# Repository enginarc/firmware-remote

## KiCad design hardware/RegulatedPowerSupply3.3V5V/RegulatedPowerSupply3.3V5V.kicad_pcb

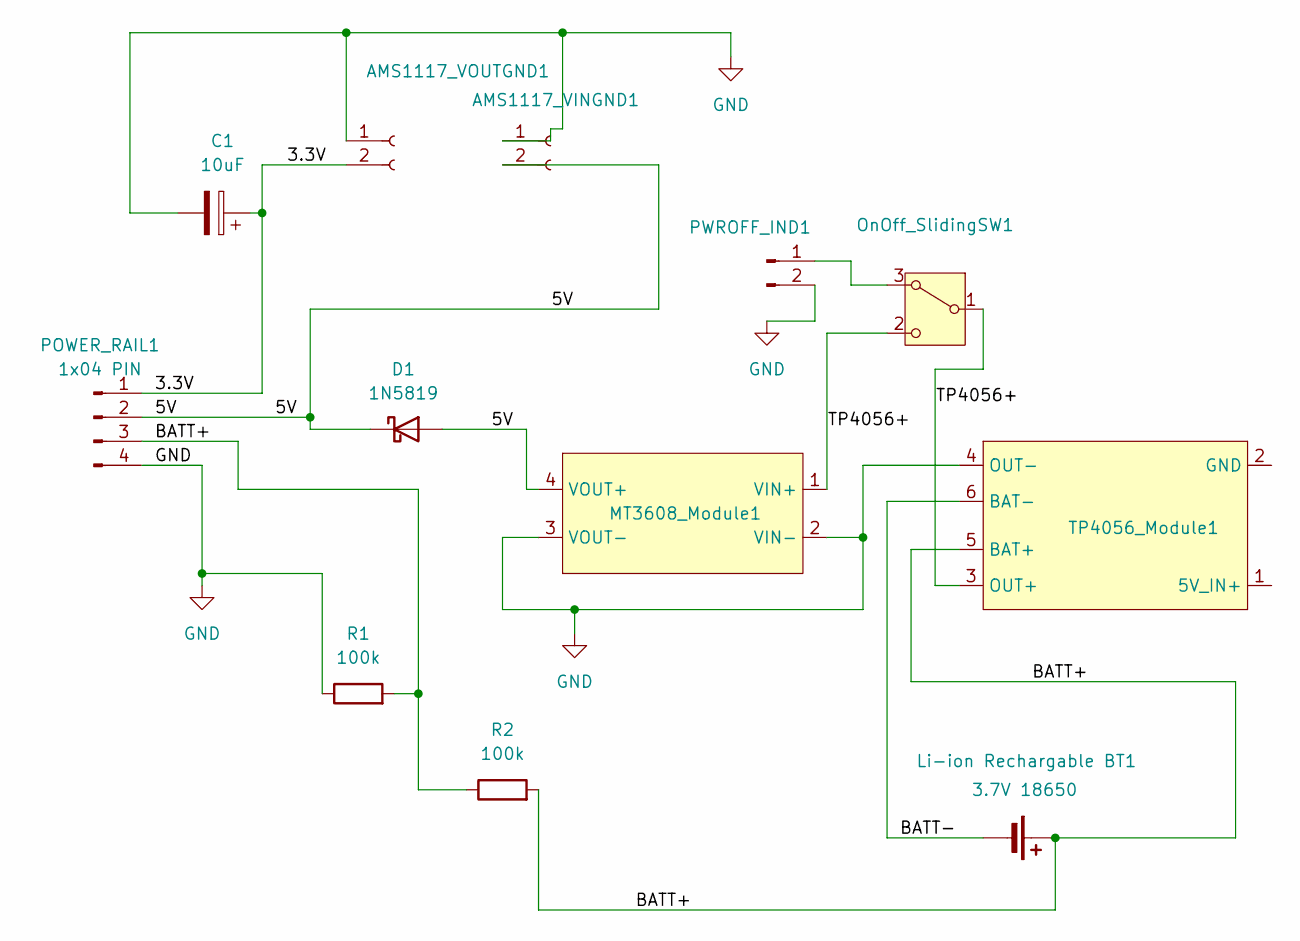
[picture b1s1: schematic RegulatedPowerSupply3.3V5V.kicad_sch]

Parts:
AMS1117_VINGND1, AMS1117_VOUTGND1: 1x02 Pin; PinSocket_1x02_P2.54mm_Vertical
C1: 10uF; CP_Radial_D4.0mm_P2.00mm
D1: 1N5819; D_DO-41_SOD81_P10.16mm_Horizontal
Li-ion Rechargable BT1: 3.7V 18650; BatteryHolder_MPD_BK-18650-PC2
MT3608_Module1: MT3608-hw-045
OnOff_SlidingSW1: SW_Wuerth_450301014042; SW_Slide-03_Wuerth-WS-SLTV_10x2.5x6.4_P2.54mm
POWER_RAIL1: 1x04 PIN; PinHeader_1x04_P2.54mm_Vertical
PWROFF_IND1: Conn_01x02_Pin; PinHeader_1x02_P2.54mm_Vertical
R1, R2: 100k; R_Axial_DIN0207_L6.3mm_D2.5mm_P7.62mm_Horizontal
TP4056_Module1: TP4056-18650

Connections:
/3.3V: AMS1117_VOUTGND1.2, C1.1, POWER_RAIL1.1
/5V: AMS1117_VINGND1.2, D1.1 (K), D1.2 (A), MT3608_Module1.4 (VOUT+), POWER_RAIL1.2
/BATT+: Li-ion Rechargable BT1.1 (+), POWER_RAIL1.3, R1.2, R2.1, R2.2, TP4056_Module1.5 (BAT+)
/BATT-: Li-ion Rechargable BT1.2 (-), TP4056_Module1.6 (BAT-)
/TP4056+: MT3608_Module1.1 (VIN+), OnOff_SlidingSW1.1 (B), OnOff_SlidingSW1.2 (C), TP4056_Module1.3 (OUT+)
GND: AMS1117_VINGND1.1, AMS1117_VOUTGND1.1, C1.2, MT3608_Module1.2 (VIN-), MT3608_Module1.3 (VOUT-), POWER_RAIL1.4, PWROFF_IND1.2, R1.1, TP4056_Module1.4 (OUT-)
unnamed: OnOff_SlidingSW1.3 (A), PWROFF_IND1.1

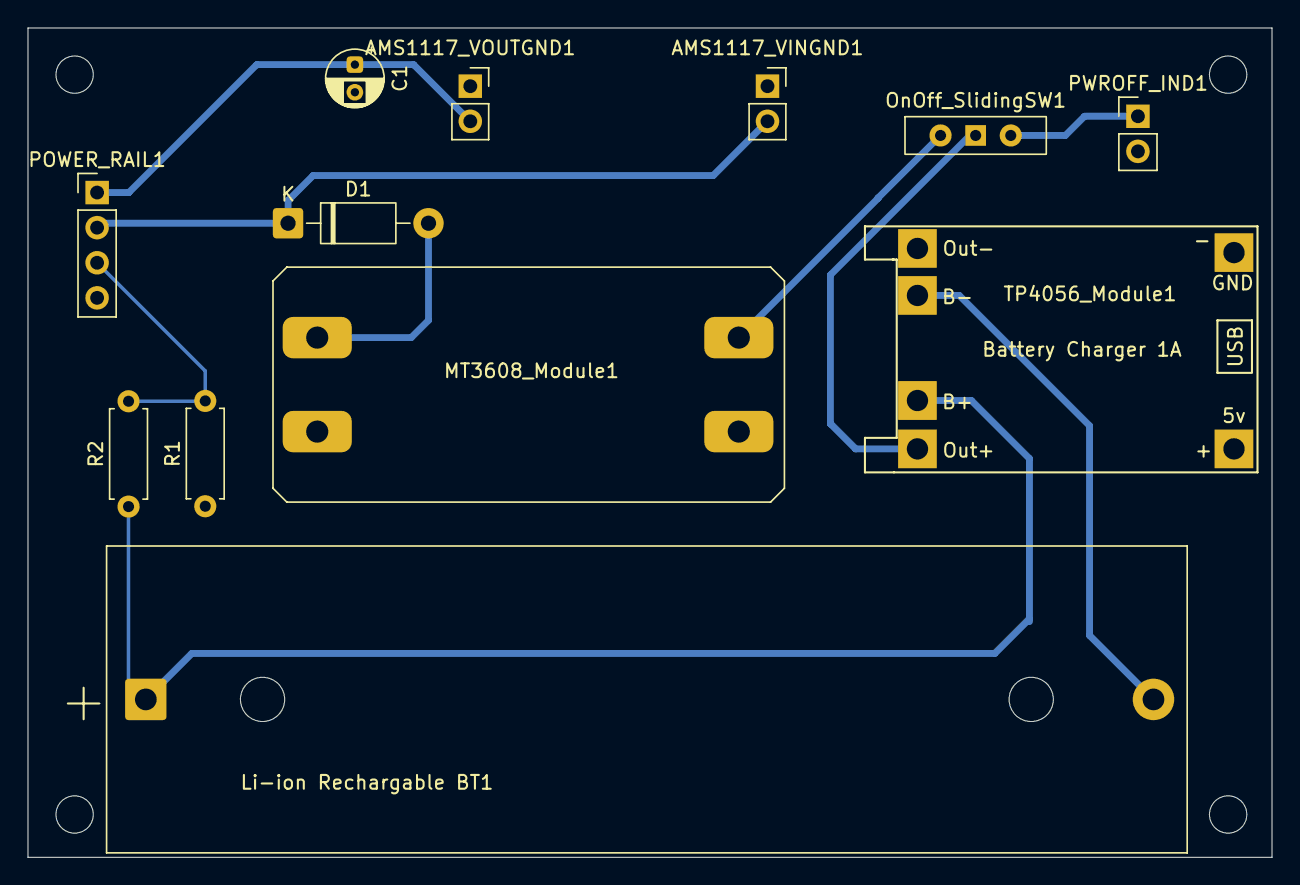
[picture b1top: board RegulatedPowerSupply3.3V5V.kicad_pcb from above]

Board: 2 copper layers, 90.0 x 60.0 mm, 12 parts (0 on the bottom side), 7 nets.

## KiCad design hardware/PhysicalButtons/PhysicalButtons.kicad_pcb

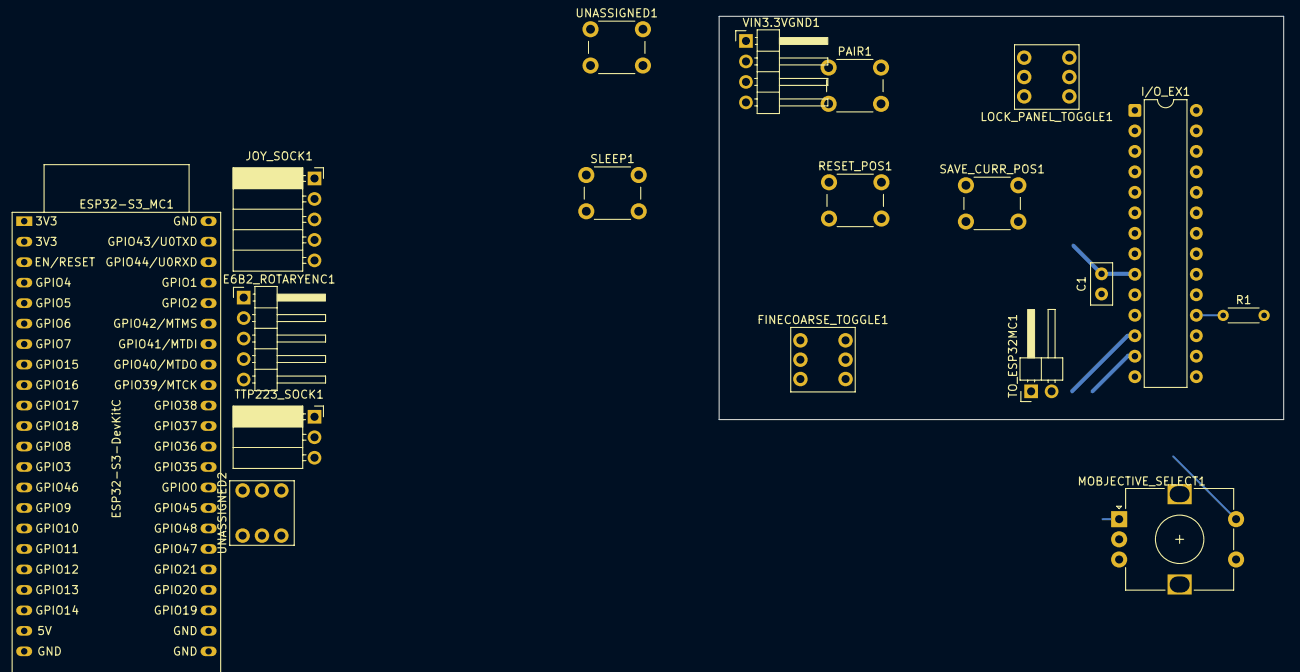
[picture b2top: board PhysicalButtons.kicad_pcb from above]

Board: 2 copper layers, 70.0 x 50.0 mm, 18 parts (0 on the bottom side), 15 nets.

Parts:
C1: 0.1uF; C_Disc_D5.0mm_W2.5mm_P2.50mm
E6B2_ROTARYENC1: Conn_01x05_Pin; PinHeader_1x05_P2.54mm_Horizontal
ESP32-S3_MC1: ESP32-S3-DevKitC
FINECOARSE_TOGGLE1: SW_Push_DPDT; SW_Push_DPDT_8x8mm
I/O_EX1: MCP23017_SP; DIP-28_W7.62mm
JOY_SOCK1: Conn_01x05_Socket; PinSocket_1x05_P2.54mm_Horizontal
LOCK_PANEL_TOGGLE1: SW_Push_DPDT; SW_Push_DPDT_8x8mm
MOBJECTIVE_SELECT1: RotaryEncoder_Switch; RotaryEncoder_Alps_EC12E-Switch_Vertical_H20mm
PAIR1: SW_Push; SW_PUSH_6mm_H8.5mm
R1: 10R; R_Axial_DIN0204_L3.6mm_D1.6mm_P5.08mm_Horizontal
RESET_POS1: SW_Push; SW_PUSH_6mm_H8.5mm
SAVE_CURR_POS1: SW_Push; SW_PUSH_6mm_H8.5mm
SLEEP1: SW_Push; SW_PUSH_6mm_H8.5mm
TO_ESP32MC1: Conn_01x02_Pin; PinHeader_1x02_P2.54mm_Horizontal
TTP223_SOCK1: Conn_01x03_Socket; PinSocket_1x03_P2.54mm_Horizontal
UNASSIGNED1: SW_Push; SW_PUSH_6mm_H8.5mm
UNASSIGNED2: SW_Push_DPDT; SW_Push_DPDT_8x8mm
VIN3.3VGND1: Conn_01x04_Pin; PinHeader_1x04_P2.54mm_Horizontal

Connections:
/<NO NET>: C1.2, ESP32-S3_MC1.1 (3V3), ESP32-S3_MC1.2 (3V3), I/O_EX1.9 (VDD), I/O_EX1.18 (~RESET), JOY_SOCK1.2, R1.1, R1.2, TTP223_SOCK1.3, VIN3.3VGND1.1
/E6B2_PHZ: E6B2_ROTARYENC1.3, E6B2_ROTARYENC1.4
/FINECOARSE_SWITCH: I/O_EX1.21 (GPA0), JOY_SOCK1.5
/LOCK_PANEL: I/O_EX1.2 (GPB1), LOCK_PANEL_TOGGLE1.2 (B)
/MCPCLK: I/O_EX1.12 (SCK), TO_ESP32MC1.1
/MCPDATA: I/O_EX1.13 (SDA), TO_ESP32MC1.2
/PAIR: I/O_EX1.1 (GPB0), PAIR1.1
/RESET_POS: I/O_EX1.3 (GPB2), RESET_POS1.1
/ROTARY_PHA: I/O_EX1.7 (GPB6), MOBJECTIVE_SELECT1.A
/ROTARY_PHB: I/O_EX1.6 (GPB5), MOBJECTIVE_SELECT1.B
/ROTARY_SW: I/O_EX1.8 (GPB7), MOBJECTIVE_SELECT1.S1
/SAVE_CURR_POS: I/O_EX1.4 (GPB3), SAVE_CURR_POS1.1
/SHUTTER_RELEASE: I/O_EX1.5 (GPB4), TTP223_SOCK1.2
/SLEEP: ESP32-S3_MC1.31 (GPIO0), SLEEP1.1
GND: C1.1, E6B2_ROTARYENC1.5, ESP32-S3_MC1.22 (GND), ESP32-S3_MC1.23 (GND), ESP32-S3_MC1.24 (GND), ESP32-S3_MC1.44 (GND), FINECOARSE_TOGGLE1.3 (C), I/O_EX1.10 (VSS), I/O_EX1.15 (A0), I/O_EX1.16 (A1), I/O_EX1.17 (A2), JOY_SOCK1.1, LOCK_PANEL_TOGGLE1.3 (C), MOBJECTIVE_SELECT1.C, MOBJECTIVE_SELECT1.S2, PAIR1.2, RESET_POS1.2, SAVE_CURR_POS1.2, SLEEP1.2, TTP223_SOCK1.1, UNASSIGNED2.3 (C), VIN3.3VGND1.4

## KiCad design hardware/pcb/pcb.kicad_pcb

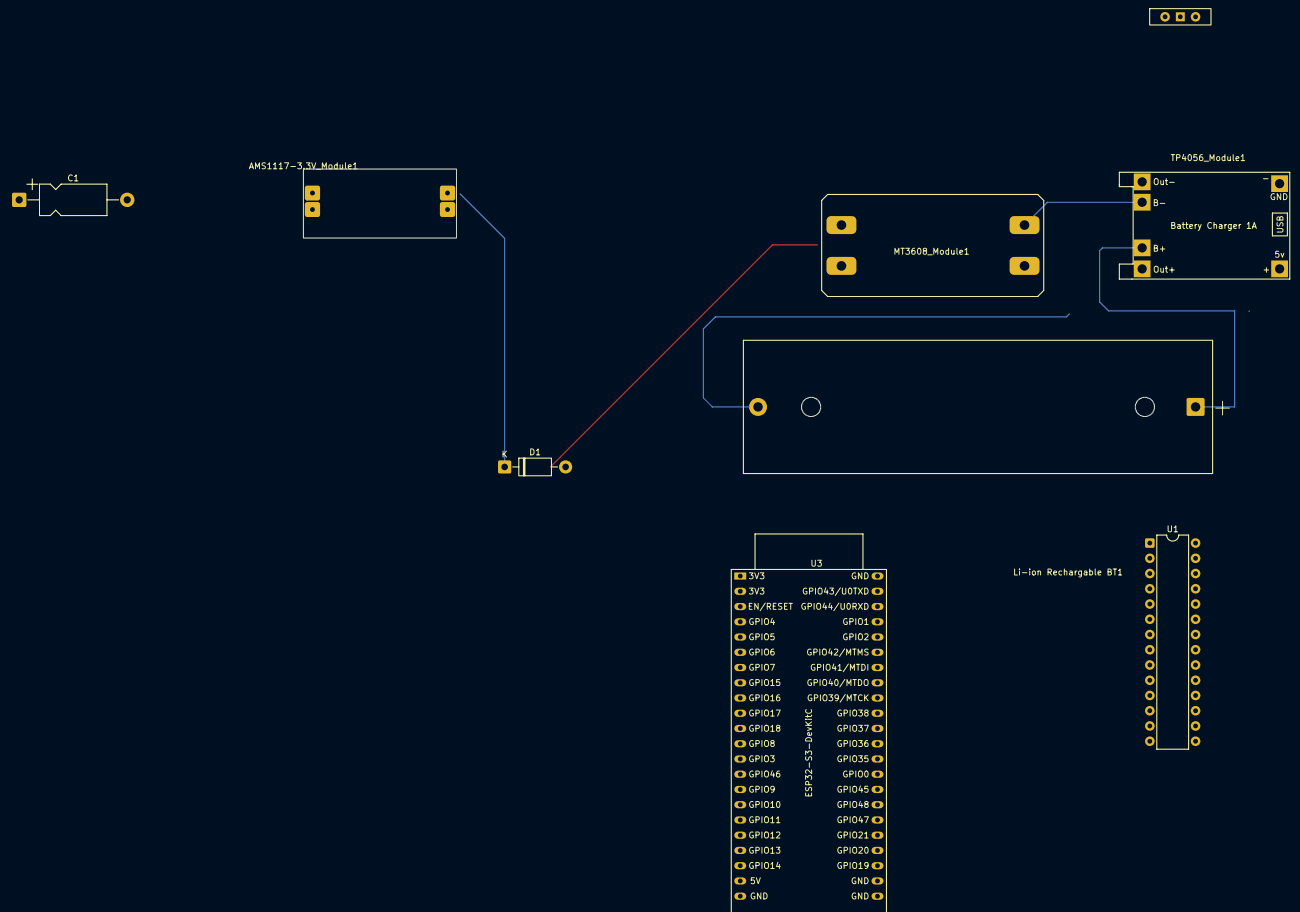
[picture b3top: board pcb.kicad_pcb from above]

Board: 2 copper layers, 9 parts (0 on the bottom side), 9 nets.

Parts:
AMS1117-3.3V_Module1: AMS1117-3.3V
C1: 10uF; CP_Axial_L11.0mm_D5.0mm_P18.00mm_Horizontal
D1: 1N5819; D_DO-41_SOD81_P10.16mm_Horizontal
Li-ion Rechargable BT1: 3.7V 18650; BatteryHolder_MPD_BK-18650-PC2
MT3608_Module1: MT3608-hw-045
OnOff_SlidingSW1: SW_Wuerth_450301014042; SW_Slide-03_Wuerth-WS-SLTV_10x2.5x6.4_P2.54mm
TP4056_Module1: TP4056-18650
U1: MCP23017_SP; DIP-28_W7.62mm
U3: ESP32-S3-DevKitC

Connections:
GND: AMS1117-3.3V_Module1.2 (GND), AMS1117-3.3V_Module1.4 (GND), C1.1, MT3608_Module1.2 (VIN-), MT3608_Module1.3 (VOUT-), TP4056_Module1.6 (BAT-)
unnamed: AMS1117-3.3V_Module1.1 (VIN+), D1.1 (K)
unnamed: AMS1117-3.3V_Module1.3 (VOUT+), C1.2, U3.1 (3V3), U3.2 (3V3)
unnamed: D1.2 (A), MT3608_Module1.4 (VOUT+)
unnamed: Li-ion Rechargable BT1.1 (+), TP4056_Module1.5 (BAT+)
unnamed: Li-ion Rechargable BT1.2 (-), TP4056_Module1.4 (OUT-)
unnamed: MT3608_Module1.1 (VIN+), OnOff_SlidingSW1.2 (C)
unnamed: OnOff_SlidingSW1.1 (B), TP4056_Module1.3 (OUT+)
unnamed: U3.22 (GND), U3.23 (GND), U3.24 (GND), U3.44 (GND)

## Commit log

2026-01-11 Initial commit of firmware-remote project
2026-01-11 Add store and display components
2026-01-13 PIN changes
2026-01-13 Init KiCad for PCB design
2026-01-16 KiCad PowerSupply
2026-01-16 gitignore updates
2026-01-17 KiCad
